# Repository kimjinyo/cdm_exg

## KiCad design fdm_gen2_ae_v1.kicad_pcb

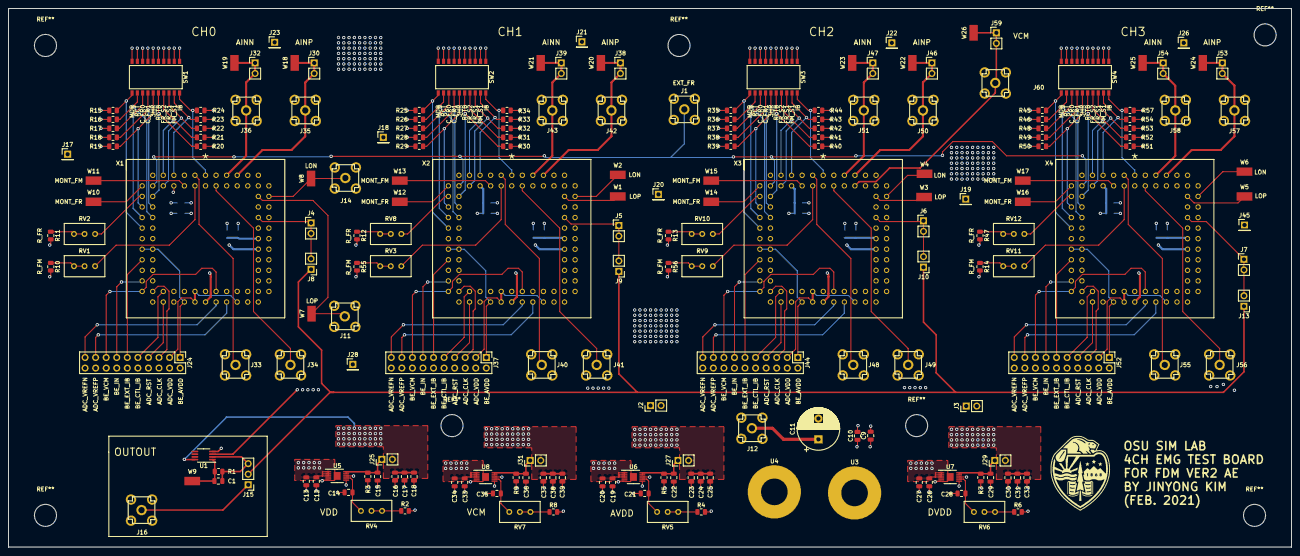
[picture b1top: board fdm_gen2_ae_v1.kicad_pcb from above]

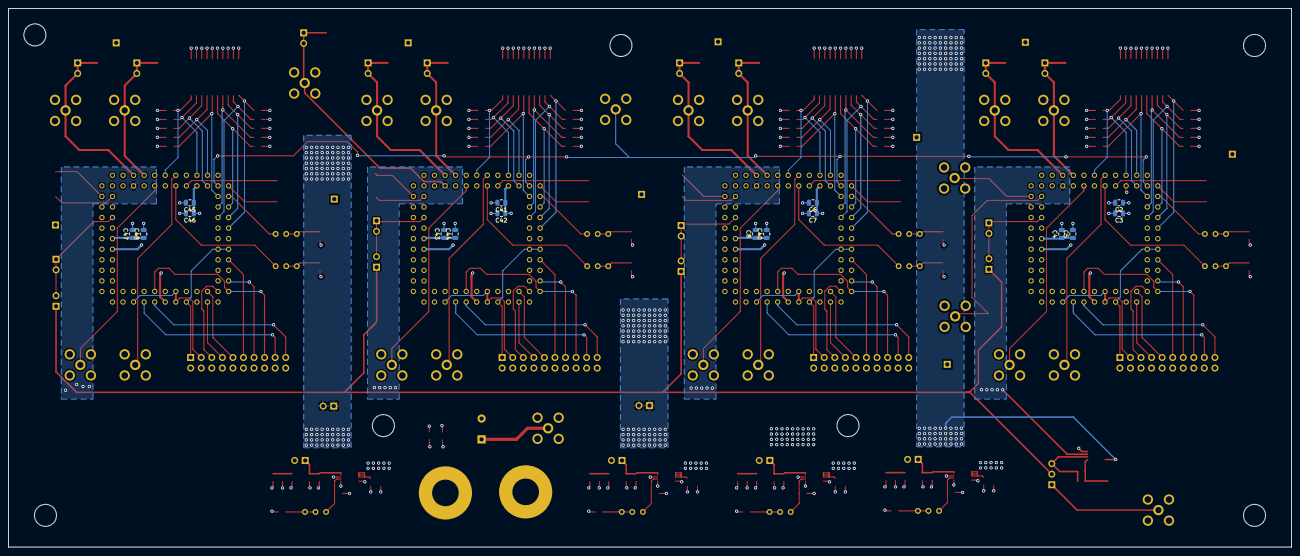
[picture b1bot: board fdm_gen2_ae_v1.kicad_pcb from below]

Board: 4 copper layers, 308.6 x 129.5 mm, 218 parts (16 on the bottom side), 155 nets.

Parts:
C1, C18, C25, C32, C39: 1n; C_0805_2012Metric
C2, C4, C6, C8, C12, C15, C16, C19, C22, C23, C26, C29, C30, C33, C36, C37, C41, C43, C45, C47: 4.7u; C_0805_2012Metric
C3, C5, C7, C13, C17, C20, C24, C27, C31, C34, C38, C40, C42, C44, C46, C48: 100n; C_0805_2012Metric
C9, C10: 0.1u; C_0805_2012Metric
C11: 500u; CP_Radial_D10.0mm_P5.00mm
C14, C21, C28, C35: 10u; C_0805_2012Metric
J1: SMA_EXT_FR; SMA_TE
J2, J3, J4, J5, J6, J7, J8, J9, J10, J13, J25, J27, J29, J30, J31, J32, J38, J39, J46, J47, J53, J54, J59: Conn_01x02; PinHeader_1x02_P2.54mm_Vertical
J11: SMA_LNA_OP; SMA_TE
J12: SMA_5p5; SMA_TE
J14: SMA_LNA_ON; SMA_TE
J15: Conn_01x03; PinHeader_1x03_P2.54mm_Vertical
J16: SMA_VDD_5p5; SMA_TE
J17, J18, J19, J20, J21, J22, J23, J26, J28, J45: Conn_01x01; PinHeader_1x01_P2.54mm_Vertical
J24, J37, J44, J52: Conn_02x10_Odd_Even; PinHeader_2x10_P2.54mm_Vertical
J33, J34, J35, J36, J40, J41, J42, J43, J48, J49, J50, J51, J55, J56, J57, J58, J60: SMA-OSU_SIM_BASIC; SMA_TE
R1: 1M; R_0805_2012Metric
R2, R3, R4, R5, R6, R7, R8, R9: 10k; R_0805_2012Metric
R10, R11, R12, R13, R14, R47, R55, R56: 0; R_0805_2012Metric
R15, R16, R17, R18, R19, R20, R21, R22, R23, R24, R25, R26, R27, R28, R29, R30, R31, R32, R33, R34, R35, R36, R37, R38, R39, R40, R41, R42, R43, R44, R45, R46, R48, R49, R50, R51, R52, R53, R54, R57: 200k; R_0805_2012Metric
RV1, RV2, RV3, RV8, RV9, RV10, RV11, RV12: R_POT-Device; Potentiometer_Bourns_3296W_Vertical
RV4, RV5, RV6, RV7: R_POT; Potentiometer_Bourns_3296W_Vertical
SW1, SW2, SW3, SW4: SW_DIP_x10; DIP-10-SW-W7.59mm
U1: LTC6256; MSOP-8_3x3mm_P0.65mm
U3, U4: BANA_PWR; MountingHole_6.4mm_M6_Pad
U5, U6, U7, U8: LT3042; MSOP-10-1EP_3x3mm_P0.5mm_EP1.68x1.88mm
W1, W2, W3, W4, W5, W6, W7, W8, W9, W10, W11, W12, W13, W14, W15, W16, W17, W18, W19, W20, W21, W22, W23, W24, W25, W26: TEST_1P; Keystone_5019
X1, X2, X3, X4: PLCC_84; PLCC_84POS

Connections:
/AVDD: C4.1, C5.1, C8.1, C23.1, C24.1, C25.1, C40.1, C43.1, C44.1, C47.1, C48.1, J2.1, J2.2, J27.2, X1.65, X1.66, X1.67, X1.74, X1.76, X2.65, X2.66, X2.67, X2.74, X2.76, X3.65, X3.66, X3.67, X3.74, X3.76, X4.65, X4.66, X4.67, X4.74, X4.76
/DVDD: C2.1, C3.1, C6.1, C7.1, C30.1, C31.1, C32.1, C41.1, C42.1, C45.1, C46.1, J3.1, J3.2, J29.2, X1.2, X1.5, X1.8, X1.23, X1.43, X1.63, X1.83, X2.2, X2.5, X2.8, X2.23, X2.43, X2.63, X2.83, X3.2, X3.5, X3.8, X3.23, X3.43, X3.63, X3.83, X4.2, X4.5, X4.8, X4.23, X4.43, X4.63, X4.83
/Regulator_AVDD/OUT: C22.1, J27.1, R5.1, U6.9, U6.10
/Regulator_AVDD/SET: C21.1, RV5.1, U6.7
/Regulator_DVDD/OUT: C29.1, J29.1, R7.1, U7.9, U7.10
/Regulator_DVDD/SET: C28.1, RV6.1, U7.7
/Regulator_PVDD/OUT: C15.1, J25.1, R3.1, U5.9, U5.10
/Regulator_PVDD/SET: C14.1, RV4.1, U5.7
/Regulator_VCM/OUT: C36.1, J31.1, R9.1, U8.9, U8.10
/Regulator_VCM/SET: C35.1, RV7.1, U8.7
/VCM: C37.1, C38.1, C39.1, J31.2, J59.1, J59.2, J60.5, U1.3, W26.1, X1.80, X2.80, X3.80, X4.80
/VDD: C16.1, C17.1, C18.1, J25.2, SW1.1, SW1.2, SW1.3, SW1.4, SW1.5, SW1.6, SW1.7, SW1.8, SW1.9, SW1.10, SW2.1, SW2.2, SW2.3, SW2.4, SW2.5, SW2.6, SW2.7, SW2.8, SW2.9, SW2.10, SW3.1, SW3.2, SW3.3, SW3.4, SW3.5, SW3.6, SW3.7, SW3.8, SW3.9, SW3.10, SW4.1, SW4.2, SW4.3, SW4.4, SW4.5, SW4.6, SW4.7, SW4.8, SW4.9, SW4.10, U1.8
/VDD_5p5: C9.1, C10.1, C11.1, C12.1, C13.1, C19.1, C20.1, C26.1, C27.1, C33.1, C34.1, J12.5, U3.1, U5.1, U5.2, U5.3, U5.6, U6.1, U6.2, U6.3, U6.6, U7.1, U7.2, U7.3, U7.6, U8.1, U8.2, U8.3, U8.6
/core/dut_AE_AINN: J32.1, J32.2, J36.5, W19.1, X1.81
/core/dut_AE_AINP: J30.1, J30.2, J35.5, W18.1, X1.79
/core/dut_AE_CTL_3HR: R19.1, SW1.15, X1.16
/core/dut_AE_CTL_C_FR<0>: R17.1, SW1.13, X1.18
/core/dut_AE_CTL_C_FR<1>: R18.1, SW1.14, X1.17
/core/dut_AE_CTL_FM_S1: R23.1, SW1.19, X1.7
/core/dut_AE_CTL_FR_S1: R22.1, SW1.18, X1.10
/core/dut_AE_CTL_FR_S2: R21.1, SW1.17, X1.9
/core/dut_AE_CTL_IB: R24.1, SW1.20, X1.1
/core/dut_AE_CTL_MDR: R15.1, SW1.11, X1.20
/core/dut_AE_CTL_RCT: R16.1, SW1.12, X1.19
/core/dut_AE_CTL_RCTB: R20.1, SW1.16, X1.15
/core/dut_AE_EXT_FM_CK: J33.5, X1.3
/core/dut_AE_EXT_FM_OR: RV1.1, X1.4
/core/dut_AE_EXT_FR_CK: J1.5, X1.13, X2.13, X3.13, X4.13
/core/dut_AE_EXT_FR_OR: RV2.1, X1.14
/core/dut_AE_EXT_IB: J34.5, X1.84
/core/dut_AE_MONT_FM: W11.1, X1.6
/core/dut_AE_MONT_FR: W10.1, X1.12
/core/dut_AE_ON_LNA: J14.5, W8.1, X1.72
/core/dut_AE_OP_LNA: J11.5, W7.1, X1.73
/core/dut_AE_OUT: J4.1, J4.2, J8.2, X1.69
/core/dut_BE_ADC_CLK: J24.5, X1.34
/core/dut_BE_ADC_RST: J24.7, X1.35
/core/dut_BE_ADC_VDD: J24.3, X1.41, X1.42, X1.49
/core/dut_BE_ADC_VREFN: J24.19, X1.45
/core/dut_BE_ADC_VREFP: J24.17, X1.47
/core/dut_BE_AVDD: J24.1, X1.24, X1.25, X1.39
/core/dut_BE_CTL_IB: J24.9, X1.36
/core/dut_BE_EXT_IB: J24.11, X1.26
/core/dut_BE_IN: J24.13, X1.30
/core/dut_BE_VCM: J24.15, X1.32, X1.46
/sheet6033DDA4/dut_AE_AINN: J54.1, J54.2, J58.5, W25.1, X4.81
/sheet6033DDA4/dut_AE_AINP: J53.1, J53.2, J57.5, W24.1, X4.79
/sheet6033DDA4/dut_AE_CTL_3HR: R50.1, SW4.15, X4.16
/sheet6033DDA4/dut_AE_CTL_C_FR<0>: R48.1, SW4.13, X4.18
/sheet6033DDA4/dut_AE_CTL_C_FR<1>: R49.1, SW4.14, X4.17
/sheet6033DDA4/dut_AE_CTL_FM_S1: R54.1, SW4.19, X4.7
/sheet6033DDA4/dut_AE_CTL_FR_S1: R53.1, SW4.18, X4.10
/sheet6033DDA4/dut_AE_CTL_FR_S2: R52.1, SW4.17, X4.9
/sheet6033DDA4/dut_AE_CTL_IB: R57.1, SW4.20, X4.1
/sheet6033DDA4/dut_AE_CTL_MDR: R45.1, SW4.11, X4.20
/sheet6033DDA4/dut_AE_CTL_RCT: R46.1, SW4.12, X4.19
/sheet6033DDA4/dut_AE_CTL_RCTB: R51.1, SW4.16, X4.15
/sheet6033DDA4/dut_AE_EXT_FM_CK: J55.5, X4.3
/sheet6033DDA4/dut_AE_EXT_FM_OR: RV11.1, X4.4
/sheet6033DDA4/dut_AE_EXT_FR_OR: RV12.1, X4.14
/sheet6033DDA4/dut_AE_EXT_IB: J56.5, X4.84
/sheet6033DDA4/dut_AE_MONT_FM: W17.1, X4.6
/sheet6033DDA4/dut_AE_MONT_FR: W16.1, X4.12
/sheet6033DDA4/dut_AE_ON_LNA: W6.1, X4.72
/sheet6033DDA4/dut_AE_OP_LNA: W5.1, X4.73
/sheet6033DDA4/dut_AE_OUT: J7.1, J7.2, J13.2, X4.69
/sheet6033DDA4/dut_BE_ADC_CLK: J52.5, X4.34
/sheet6033DDA4/dut_BE_ADC_RST: J52.7, X4.35
/sheet6033DDA4/dut_BE_ADC_VDD: J52.3, X4.41, X4.42, X4.49
/sheet6033DDA4/dut_BE_ADC_VREFN: J52.19, X4.45
/sheet6033DDA4/dut_BE_ADC_VREFP: J52.17, X4.47
/sheet6033DDA4/dut_BE_AVDD: J52.1, X4.24, X4.25, X4.39
/sheet6033DDA4/dut_BE_CTL_IB: J52.9, X4.36
/sheet6033DDA4/dut_BE_EXT_IB: J52.11, X4.26
/sheet6033DDA4/dut_BE_IN: J52.13, X4.30
/sheet6033DDA4/dut_BE_VCM: J52.15, X4.32, X4.46
/sheet6040185E/dut_AE_AINN: J39.1, J39.2, J43.5, W21.1, X2.81
/sheet6040185E/dut_AE_AINP: J38.1, J38.2, J42.5, W20.1, X2.79
/sheet6040185E/dut_AE_CTL_3HR: R29.1, SW2.15, X2.16
/sheet6040185E/dut_AE_CTL_C_FR<0>: R27.1, SW2.13, X2.18
/sheet6040185E/dut_AE_CTL_C_FR<1>: R28.1, SW2.14, X2.17
/sheet6040185E/dut_AE_CTL_FM_S1: R33.1, SW2.19, X2.7
/sheet6040185E/dut_AE_CTL_FR_S1: R32.1, SW2.18, X2.10
/sheet6040185E/dut_AE_CTL_FR_S2: R31.1, SW2.17, X2.9
/sheet6040185E/dut_AE_CTL_IB: R34.1, SW2.20, X2.1
/sheet6040185E/dut_AE_CTL_MDR: R25.1, SW2.11, X2.20
/sheet6040185E/dut_AE_CTL_RCT: R26.1, SW2.12, X2.19
/sheet6040185E/dut_AE_CTL_RCTB: R30.1, SW2.16, X2.15
/sheet6040185E/dut_AE_EXT_FM_CK: J40.5, X2.3
/sheet6040185E/dut_AE_EXT_FM_OR: RV3.1, X2.4
/sheet6040185E/dut_AE_EXT_FR_OR: RV8.1, X2.14
/sheet6040185E/dut_AE_EXT_IB: J41.5, X2.84
/sheet6040185E/dut_AE_MONT_FM: W13.1, X2.6
/sheet6040185E/dut_AE_MONT_FR: W12.1, X2.12
/sheet6040185E/dut_AE_ON_LNA: W2.1, X2.72
/sheet6040185E/dut_AE_OP_LNA: W1.1, X2.73
/sheet6040185E/dut_AE_OUT: J5.1, J5.2, J9.2, X2.69
/sheet6040185E/dut_BE_ADC_CLK: J37.5, X2.34
/sheet6040185E/dut_BE_ADC_RST: J37.7, X2.35
/sheet6040185E/dut_BE_ADC_VDD: J37.3, X2.41, X2.42, X2.49
/sheet6040185E/dut_BE_ADC_VREFN: J37.19, X2.45
/sheet6040185E/dut_BE_ADC_VREFP: J37.17, X2.47
/sheet6040185E/dut_BE_AVDD: J37.1, X2.24, X2.25, X2.39
/sheet6040185E/dut_BE_CTL_IB: J37.9, X2.36
/sheet6040185E/dut_BE_EXT_IB: J37.11, X2.26
/sheet6040185E/dut_BE_IN: J37.13, X2.30
/sheet6040185E/dut_BE_VCM: J37.15, X2.32, X2.46
/sheet60406999/dut_AE_AINN: J47.1, J47.2, J51.5, W23.1, X3.81
/sheet60406999/dut_AE_AINP: J46.1, J46.2, J50.5, W22.1, X3.79
/sheet60406999/dut_AE_CTL_3HR: R39.1, SW3.15, X3.16
/sheet60406999/dut_AE_CTL_C_FR<0>: R37.1, SW3.13, X3.18
/sheet60406999/dut_AE_CTL_C_FR<1>: R38.1, SW3.14, X3.17
/sheet60406999/dut_AE_CTL_FM_S1: R43.1, SW3.19, X3.7
/sheet60406999/dut_AE_CTL_FR_S1: R42.1, SW3.18, X3.10
/sheet60406999/dut_AE_CTL_FR_S2: R41.1, SW3.17, X3.9
/sheet60406999/dut_AE_CTL_IB: R44.1, SW3.20, X3.1
/sheet60406999/dut_AE_CTL_MDR: R35.1, SW3.11, X3.20
/sheet60406999/dut_AE_CTL_RCT: R36.1, SW3.12, X3.19
/sheet60406999/dut_AE_CTL_RCTB: R40.1, SW3.16, X3.15
/sheet60406999/dut_AE_EXT_FM_CK: J48.5, X3.3
/sheet60406999/dut_AE_EXT_FM_OR: RV9.1, X3.4
/sheet60406999/dut_AE_EXT_FR_OR: RV10.1, X3.14
/sheet60406999/dut_AE_EXT_IB: J49.5, X3.84
/sheet60406999/dut_AE_MONT_FM: W15.1, X3.6
/sheet60406999/dut_AE_MONT_FR: W14.1, X3.12
/sheet60406999/dut_AE_ON_LNA: W4.1, X3.72
/sheet60406999/dut_AE_OP_LNA: W3.1, X3.73
/sheet60406999/dut_AE_OUT: J6.1, J6.2, J10.2, X3.69
/sheet60406999/dut_BE_ADC_CLK: J44.5, X3.34
/sheet60406999/dut_BE_ADC_RST: J44.7, X3.35
/sheet60406999/dut_BE_ADC_VDD: J44.3, X3.41, X3.42, X3.49
/sheet60406999/dut_BE_ADC_VREFN: J44.19, X3.45
/sheet60406999/dut_BE_ADC_VREFP: J44.17, X3.47
/sheet60406999/dut_BE_AVDD: J44.1, X3.24, X3.25, X3.39
/sheet60406999/dut_BE_CTL_IB: J44.9, X3.36
/sheet60406999/dut_BE_EXT_IB: J44.11, X3.26
/sheet60406999/dut_BE_IN: J44.13, X3.30
/sheet60406999/dut_BE_VCM: J44.15, X3.32, X3.46
GND: C2.2, C3.2, C4.2, C5.2, C6.2, C7.2, C8.2, C9.2, C10.2, C11.2, C12.2, C13.2, C14.2, C15.2, C16.2, C17.2, C18.2, C19.2, C20.2, C21.2, C22.2, C23.2, C24.2, C25.2, C26.2, C27.2, C28.2, C29.2, C30.2, C31.2, C32.2, C33.2, C34.2, C35.2, C36.2, C37.2, C38.2, C39.2, C40.2, C41.2, C42.2, C43.2, C44.2, C45.2, C46.2, C47.2, C48.2, J1.1, J1.2, J1.3, J1.4, J11.1, J11.2, J11.3, J11.4, J12.1, J12.2, J12.3, J12.4, J14.1, J14.2, J14.3, J14.4, J16.1, J16.2, J16.3, J16.4, J17.1, J18.1, J19.1, J20.1, J21.1, J22.1, J23.1, J24.2, J24.4, J24.6, J24.8, J24.10, J24.12, J24.14, J24.16, J24.18, J24.20, J26.1, J28.1, J33.1, J33.2, J33.3, J33.4, J34.1, J34.2, J34.3, J34.4, J35.1, J35.2, J35.3, J35.4, J36.1, J36.2, J36.3, J36.4, J37.2, J37.4, J37.6, J37.8, J37.10, J37.12, J37.14, J37.16, J37.18, J37.20, J40.1, J40.2, J40.3, J40.4, J41.1, J41.2, J41.3, J41.4, J42.1, J42.2, J42.3, J42.4, J43.1, J43.2, J43.3, J43.4, J44.2, J44.4, J44.6, J44.8, J44.10, J44.12, J44.14, J44.16, J44.18, J44.20, J45.1, J48.1, J48.2, J48.3, J48.4, J49.1, J49.2, J49.3, J49.4, J50.1, J50.2, J50.3, J50.4, J51.1, J51.2, J51.3, J51.4, J52.2, J52.4, J52.6, J52.8, J52.10, J52.12, J52.14, J52.16, J52.18, J52.20, J55.1, J55.2, J55.3, J55.4, J56.1, J56.2, J56.3, J56.4, J57.1, J57.2, J57.3, J57.4, J58.1, J58.2, J58.3, J58.4, J60.1, J60.2, J60.3, J60.4, R2.2, R3.2, R4.2, R5.2, R6.2, R7.2, R8.2, R9.2, R10.2, R11.2, R12.2, R13.2, R14.2, R15.2, R16.2, R17.2, R18.2, R19.2, R20.2, R21.2, R22.2, R23.2, R24.2, R25.2, R26.2, R27.2, R28.2, R29.2, R30.2, R31.2, R32.2, R33.2, R34.2, R35.2, R36.2, R37.2, R38.2, R39.2, R40.2, R41.2, R42.2, R43.2, R44.2, R45.2, R46.2, R47.2, R48.2, R49.2, R50.2, R51.2, R52.2, R53.2, R54.2, R55.2, R56.2, R57.2, U1.4, U4.1, U5.5, U5.8, U6.5, U6.8, U7.5, U7.8, U8.5, U8.8, X1.11, X1.21, X1.22, X1.27, X1.28, X1.31, X1.33, X1.40, X1.44, X1.48, X1.62, X1.64, X1.68, X1.70, X1.71, X1.75, X1.77, X1.78, X1.82, X2.11, X2.21, X2.22, X2.27, X2.28, X2.31, X2.33, X2.40, X2.44, X2.48, X2.62, X2.64, X2.68, X2.70, X2.71, X2.75, X2.77, X2.78, X2.82, X3.11, X3.21, X3.22, X3.27, X3.28, X3.31, X3.33, X3.40, X3.44, X3.48, X3.62, X3.64, X3.68, X3.70, X3.71, X3.75, X3.77, X3.78, X3.82, X4.11, X4.21, X4.22, X4.27, X4.28, X4.31, X4.33, X4.40, X4.44, X4.48, X4.62, X4.64, X4.68, X4.70, X4.71, X4.75, X4.77, X4.78, X4.82
unnamed: C1.1, J15.3, R1.2, U1.2
unnamed: C1.2, R1.1, U1.1, W9.1
unnamed: J8.1, J9.1, J10.1, J13.1, J15.2
unnamed: J15.1, J16.5
unnamed: R2.1, RV4.2, RV4.3
unnamed: R4.1, RV5.2, RV5.3
unnamed: R6.1, RV6.2, RV6.3
unnamed: R8.1, RV7.2, RV7.3
unnamed: R10.1, RV1.2, RV1.3
unnamed: R11.1, RV2.2, RV2.3
unnamed: R12.1, RV8.2, RV8.3
unnamed: R13.1, RV10.2, RV10.3
unnamed: R14.1, RV11.2, RV11.3
unnamed: R47.1, RV12.2, RV12.3
unnamed: R55.1, RV3.2, RV3.3
unnamed: R56.1, RV9.2, RV9.3

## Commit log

2021-02-21 Feb20 commit
